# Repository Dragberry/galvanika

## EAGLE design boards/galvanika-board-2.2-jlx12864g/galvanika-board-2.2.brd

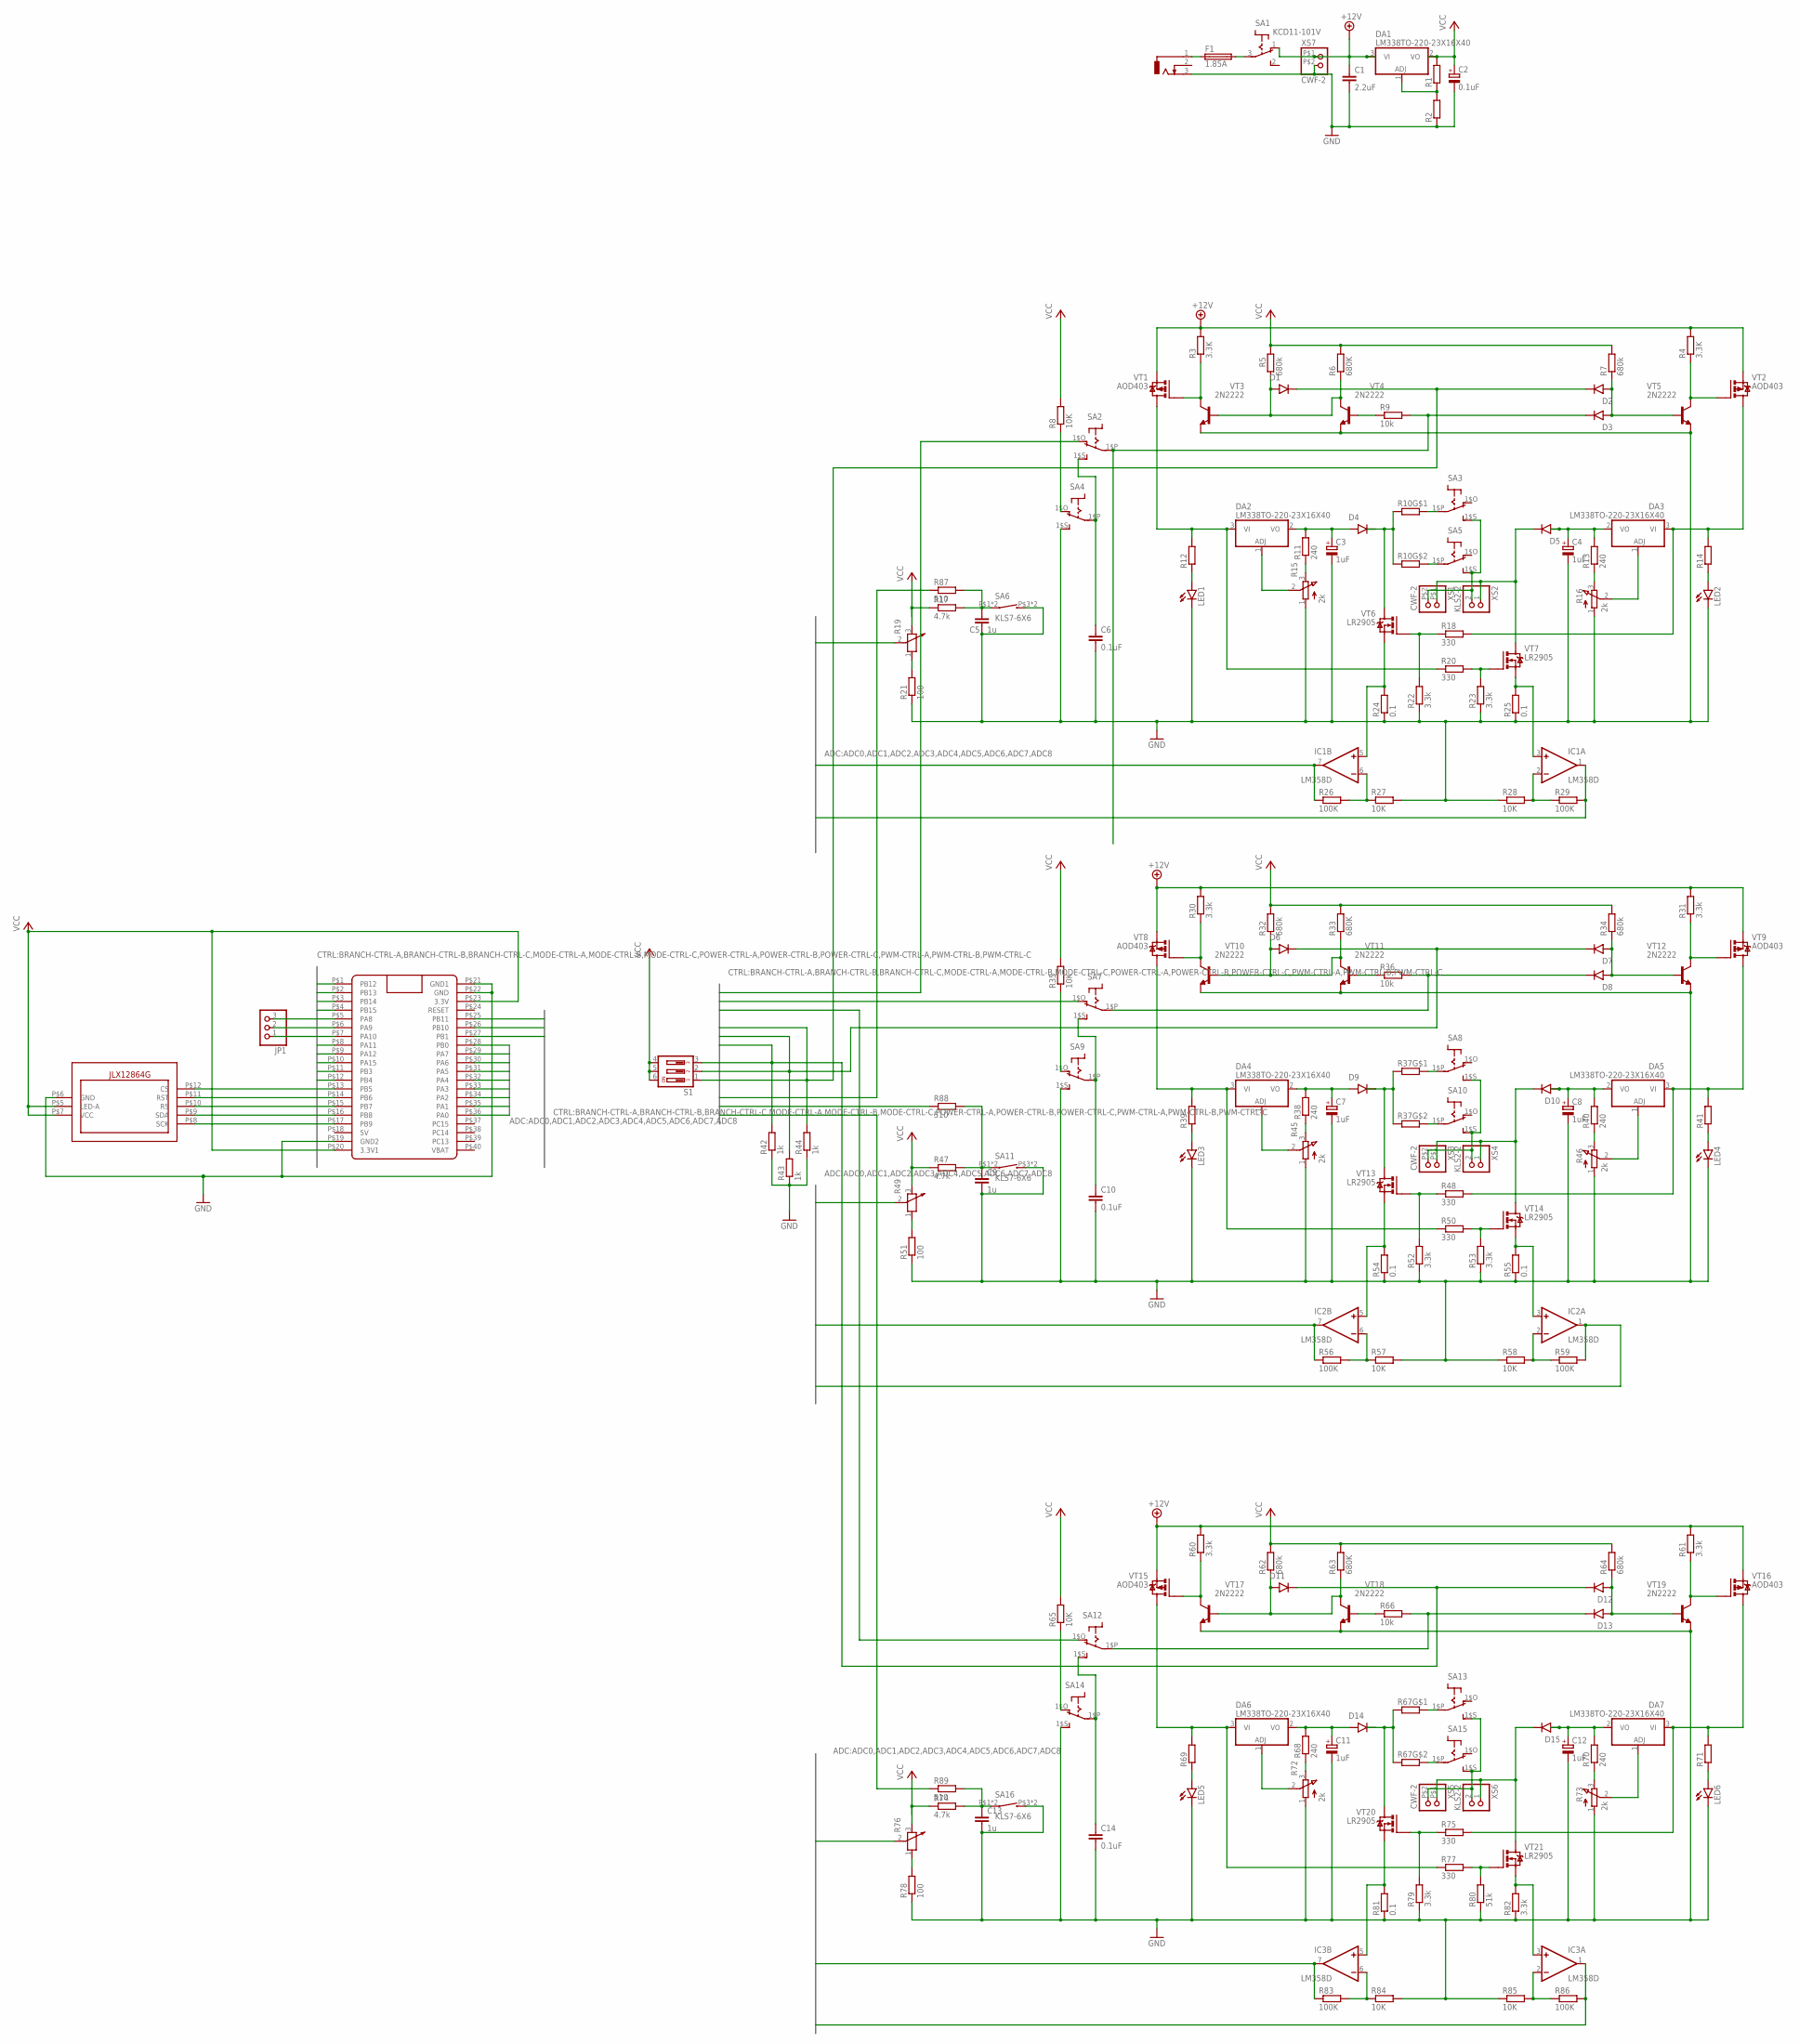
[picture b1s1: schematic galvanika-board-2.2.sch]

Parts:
C1: 2.2uF; C025-025X050
C2: 0.1uF; E2,5-5
C3, C4, C7, C8, C11, C12: 1uF; E5-4
C5, C9, C13: 1u; C1206
C6, C10, C14: 0.1uF; C1206
D1, D2, D3, D4, D5, D6, D7, D8, D9, D10, D11, D12, D13, D14, D15: 1N4001; DO41-10
DA1, DA2, DA3, DA4, DA5, DA6, DA7: LM338TO-220-23X16X40; TO220-23X16X40
DD1: BLUE_PILL
F1: 1.85A; MF-R
HG1: JLX12864G
IC1, IC2, IC3: LM358D; SO08
J1: DCJ0303
JP1: PINHD-1X3; 1X03
LED1, LED2, LED3, LED4, LED5, LED6: LED3MM
R1, R2, R12, R14, R39, R41, R69, R71: R-EU_0207/10; 0207/10
R3, R4: 3.3K; 0207/10
R5, R7, R32, R34, R62, R64: 680k; 0207/10
R6, R33, R63: 680K; 0207/10
R8, R35, R65: 10K; 0207/10
R9, R36, R66: 10k; 0207/10
R10, R37, R67: SQP-5W-2
R11, R13, R38, R40, R68, R70: 240; 0207/10
R15, R16, R45, R46, R72, R73: 2k; 3RP/1610N
R17, R47, R74: 4.7k; R1206
R18, R20, R48, R50, R75, R77: 330; 0207/10
R19, R49, R76: R0904N
R21, R51, R78: 100; R1206
R22, R23, R30, R31, R52, R53, R60, R61, R79: 3.3k; 0207/10
R24, R25, R54, R55, R81: 0.1; 0411/12
R26, R29, R56, R59, R83, R86: 100K; R1206
R27, R28, R57, R58, R84, R85: 10K; R1206
R42, R43, R44: 1k; R1206
R80: 51k; 0207/10
R82: 3.3k; 0411/12
R87, R88, R89: 510; R1206
S1: DS03; DS-03
SA1: KCD11-101V; KCD11-101-V
SA2, SA3, SA4, SA5, SA7, SA8, SA9, SA10, SA12, SA13, SA14, SA15: SS12D00DIP; SS12D00
SA6, SA11, SA16: KLS7-6X6
VT1, VT2, VT8, VT9, VT15, VT16: AOD403; TO252
VT3, VT4, VT5, VT10, VT11, VT12, VT17, VT18, VT19: 2N2222; TO92
VT6, VT7, VT13, VT14, VT20, VT21: LR2905; TO252
XS1, XS3, XS5, XS7: CWF-2
XS2, XS4, XS6: KLS2-2

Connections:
+12V: C1.1, DA1.3 (VI), R3.2, R4.2, R30.2, R31.2, R60.2, R61.2, SA1.1 (O), VT1.2 (S), VT2.2 (S), VT8.2 (S), VT9.2 (S), VT15.2 (S), VT16.2 (S), XS7.P$1 (1)
A-LEFT: IC1.3 (+IN), R25.2, VT7.2 (S)
A-LEFT1: IC2.3 (+IN), R55.2, VT14.2 (S)
A-LEFT2: IC3.3 (+IN), R82.2, VT21.2 (S)
A-RIGHT: IC1.5 (+IN), R24.2, VT6.2 (S)
A-RIGHT1: IC2.5 (+IN), R54.2, VT13.2 (S)
A-RIGHT2: IC3.5 (+IN), R81.2, VT20.2 (S)
ADC0: DD1.P$36 (PA0), R19.2 (3)
ADC1: DD1.P$35 (PA1), R49.2 (3)
ADC2: DD1.P$34 (PA2), IC1.7 (OUT), R26.1
ADC3: DD1.P$33 (PA3), IC1.1 (OUT), R29.2
ADC4: DD1.P$32 (PA4), R76.2 (3)
ADC5: DD1.P$31 (PA5), IC2.1 (OUT), R59.2
ADC6: DD1.P$30 (PA6), IC2.7 (OUT), R56.1
ADC7: DD1.P$29 (PA7), IC3.7 (OUT), R83.1
ADC8: DD1.P$28 (PB0), IC3.1 (OUT), R86.2
BRANCH-CTRL-A: D3.C (CATHODE), DD1.P$9 (PA12), R9.2, SA2.1$P
BRANCH-CTRL-B: D8.C (CATHODE), DD1.P$8 (PA11), R36.2, SA7.1$P
BRANCH-CTRL-C: D13.C (CATHODE), DD1.P$4 (PB15), R66.2, SA12.1$P
GND: C1.2, C2.-, C3.-, C4.-, C5.2, C6.2, C7.-, C8.-, C9.2, C10.2, C11.-, C12.-, C13.2, C14.2, DD1.P$19 (GND2), DD1.P$21 (GND1), DD1.P$22 (GND), HG1.P$6 (GND), IC1.4 (V-), IC2.4 (V-), IC3.4 (V-), J1.3, LED1.K (C), LED2.K (C), LED3.K (C), LED4.K (C), LED5.K (C), LED6.K (C), R2.1, R15.1 (A), R16.1 (A), R21.1, R22.1, R23.1, R24.1, R25.1, R27.2, R28.1, R42.1, R43.1, R44.1, R45.1 (A), R46.1 (A), R51.1, R52.1, R53.1, R54.1, R55.1, R57.2, R58.1, R72.1 (A), R73.1 (A), R78.1, R79.1, R80.1, R81.1, R82.1, R84.2, R85.1, SA4.1$S (S), SA6.P$3 (2), SA6.P$4 (2), SA9.1$S (S), SA11.P$3 (2), SA11.P$4 (2), SA14.1$S (S), SA16.P$3 (2), SA16.P$4 (2), VT3.3 (E), VT4.3 (E), VT5.3 (E), VT10.3 (E), VT11.3 (E), VT12.3 (E), VT17.3 (E), VT18.3 (E), VT19.3 (E), XS7.P$2 (2)
MODE-CTRL-A: DD1.P$12 (PB4), R87.1
MODE-CTRL-B: DD1.P$11 (PB3), R88.1
MODE-CTRL-C: DD1.P$10 (PA15), R89.1
unnamed: R3.1, VT1.1 (G), VT3.1 (C)
unnamed: DD1.P$15 (PB7), HG1.P$10 (RS)
unnamed: R10.4 (2), SA5.1$P
unnamed: DA1.1 (ADJ), R1.1, R2.2
unnamed: R30.1, VT8.1 (G), VT10.1 (C)
unnamed: R9.1, VT4.2 (B)
unnamed: D1.A (ANODE), R5.1, R6.1, VT3.2 (B), VT4.1 (C)
unnamed: LED1.A, R12.1
unnamed: R11.1, R15.3 (E)
unnamed: DA2.1 (ADJ), R15.2 (S)
unnamed: DD1.P$14 (PB6), HG1.P$11 (RST)
unnamed: R18.1, R22.2, VT6.1 (G)
unnamed: D4.C (CATHODE), R10.1, R10.3 (1), VT6.3 (D)
unnamed: R10.2, SA3.1$P
unnamed: R20.2, R23.2, VT7.1 (G)
unnamed: D2.A (ANODE), D3.A (ANODE), R7.1, VT5.2 (B)
unnamed: C5.1, R17.2, R87.2, SA6.P$1 (1), SA6.P$2 (1)
unnamed: R36.1, VT11.2 (B)
unnamed: LED2.A, R14.1
unnamed: R4.1, VT2.1 (G), VT5.1 (C)
unnamed: R13.1, R16.3 (E)
unnamed: LED3.A, R39.1
unnamed: DA3.1 (ADJ), R16.2 (S)
unnamed: DA4.1 (ADJ), R45.2 (S)
unnamed: D9.C (CATHODE), R37.1, R37.3 (1), VT13.3 (D)
unnamed: IC1.6 (-IN), R26.2, R27.1
unnamed: IC1.2 (-IN), R28.2, R29.1
unnamed: C9.1, R47.2, R88.2, SA11.P$1 (1), SA11.P$2 (1)
unnamed: DA5.1 (ADJ), R46.2 (S)
unnamed: LED4.A, R41.1
unnamed: R31.1, VT9.1 (G), VT12.1 (C)
unnamed: C13.1, R74.2, R89.2, SA16.P$1 (1), SA16.P$2 (1)
unnamed: IC2.6 (-IN), R56.2, R57.1
unnamed: IC2.2 (-IN), R58.2, R59.1
unnamed: DD1.P$5 (PA8), JP1.3
unnamed: D10.C (CATHODE), VT14.3 (D), XS3.P$1 (1), XS4.1
unnamed: R37.4 (2), SA10.1$P
unnamed: R37.2, SA8.1$P
unnamed: SA8.1$S (S), SA10.1$S (S), XS3.P$2 (2), XS4.2
unnamed: R48.1, R52.2, VT13.1 (G)
unnamed: R50.2, R53.2, VT14.1 (G)
unnamed: R38.1, R45.3 (E)
unnamed: R40.1, R46.3 (E)
unnamed: C10.1, SA7.1$S (S), SA9.1$P
unnamed: DD1.P$6 (PA9), JP1.2
unnamed: D6.A (ANODE), R32.1, R33.1, VT10.2 (B), VT11.1 (C)
unnamed: D7.A (ANODE), D8.A (ANODE), R34.1, VT12.2 (B)
unnamed: DD1.P$7 (PA10), JP1.1
unnamed: R60.1, VT15.1 (G), VT17.1 (C)
unnamed: R66.1, VT18.2 (B)
unnamed: LED5.A, R69.1
unnamed: DA6.1 (ADJ), R72.2 (S)
unnamed: D14.C (CATHODE), R67.1, R67.3 (1), VT20.3 (D)
unnamed: DA7.1 (ADJ), R73.2 (S)
unnamed: LED6.A, R71.1
unnamed: R61.1, VT16.1 (G), VT19.1 (C)
unnamed: D5.C (CATHODE), VT7.3 (D), XS1.P$1 (1), XS2.1
unnamed: F1.1, J1.1
unnamed: SA3.1$S (S), SA5.1$S (S), XS1.P$2 (2), XS2.2
unnamed: IC3.6 (-IN), R83.2, R84.1
unnamed: F1.2, SA1.3
unnamed: IC3.2 (-IN), R85.2, R86.1
unnamed: D15.C (CATHODE), VT21.3 (D), XS5.P$1 (1), XS6.1
unnamed: R67.4 (2), SA15.1$P
unnamed: R67.2, SA13.1$P
unnamed: SA13.1$S (S), SA15.1$S (S), XS5.P$2 (2), XS6.2
unnamed: R75.1, R79.2, VT20.1 (G)
unnamed: R77.2, R80.2, VT21.1 (G)
unnamed: R68.1, R72.3 (E)
unnamed: R70.1, R73.3 (E)
unnamed: C14.1, SA12.1$S (S), SA14.1$P
unnamed: DD1.P$16 (PB8), HG1.P$9 (SDA)
unnamed: D11.A (ANODE), R62.1, R63.1, VT17.2 (B), VT18.1 (C)
unnamed: D12.A (ANODE), D13.A (ANODE), R64.1, VT19.2 (B)
unnamed: DD1.P$17 (PB9), HG1.P$8 (SCK)
unnamed: DD1.P$13 (PB5), HG1.P$12 (CS)
unnamed: R19.1, R21.2
unnamed: R49.1, R51.2
unnamed: C6.1, SA2.1$S (S), SA4.1$P
unnamed: R76.1, R78.2
POWER-CTRL-A: D1.C (CATHODE), D2.C (CATHODE), DD1.P$27 (PB1), R44.2, S1.1
POWER-CTRL-B: D6.C (CATHODE), D7.C (CATHODE), DD1.P$26 (PB10), R43.2, S1.2
POWER-CTRL-C: D11.C (CATHODE), D12.C (CATHODE), DD1.P$25 (PB11), R42.2, S1.3
PWM-CTRL-A: DD1.P$2 (PB13), SA2.1$O (O)
PWM-CTRL-B: DD1.P$3 (PB14), SA7.1$O (O)
PWM-CTRL-C: DD1.P$1 (PB12), SA12.1$O (O)
RIGHT-EN: R8.1, SA4.1$O (O)
RIGHT-EN1: R35.1, SA9.1$O (O)
RIGHT-EN2: R65.1, SA14.1$O (O)
VCC: C2.+, DA1.2 (VO), DD1.P$20 (3.3V1), DD1.P$23 (3.3V), HG1.P$5 (LED-A), HG1.P$7 (VCC), IC1.8 (V+), IC2.8 (V+), IC3.8 (V+), R1.2, R5.2, R6.2, R7.2, R8.2, R17.1, R19.3 (2), R32.2, R33.2, R34.2, R35.2, R47.1, R49.3 (2), R62.2, R63.2, R64.2, R65.2, R74.1, R76.3 (2), S1.4, S1.5, S1.6
VI-LEFT: DA2.3 (VI), R12.2, R20.1, VT1.3 (D)
VI-LEFT1: DA4.3 (VI), R39.2, R50.1, VT8.3 (D)
VI-LEFT2: DA6.3 (VI), R69.2, R77.1, VT15.3 (D)
VI-RIGHT: DA3.3 (VI), R14.2, R18.2, VT2.3 (D)
VI-RIGHT1: DA5.3 (VI), R41.2, R48.2, VT9.3 (D)
VI-RIGHT2: DA7.3 (VI), R71.2, R75.2, VT16.3 (D)
VO-LEFT: C3.+, D4.A (ANODE), DA2.2 (VO), R11.2
VO-LEFT1: C7.+, D9.A (ANODE), DA4.2 (VO), R38.2
VO-LEFT2: C11.+, D14.A (ANODE), DA6.2 (VO), R68.2
VO-RIGHT: C4.+, D5.A (ANODE), DA3.2 (VO), R13.2
VO-RIGHT1: C8.+, D10.A (ANODE), DA5.2 (VO), R40.2
VO-RIGHT2: C12.+, D15.A (ANODE), DA7.2 (VO), R70.2

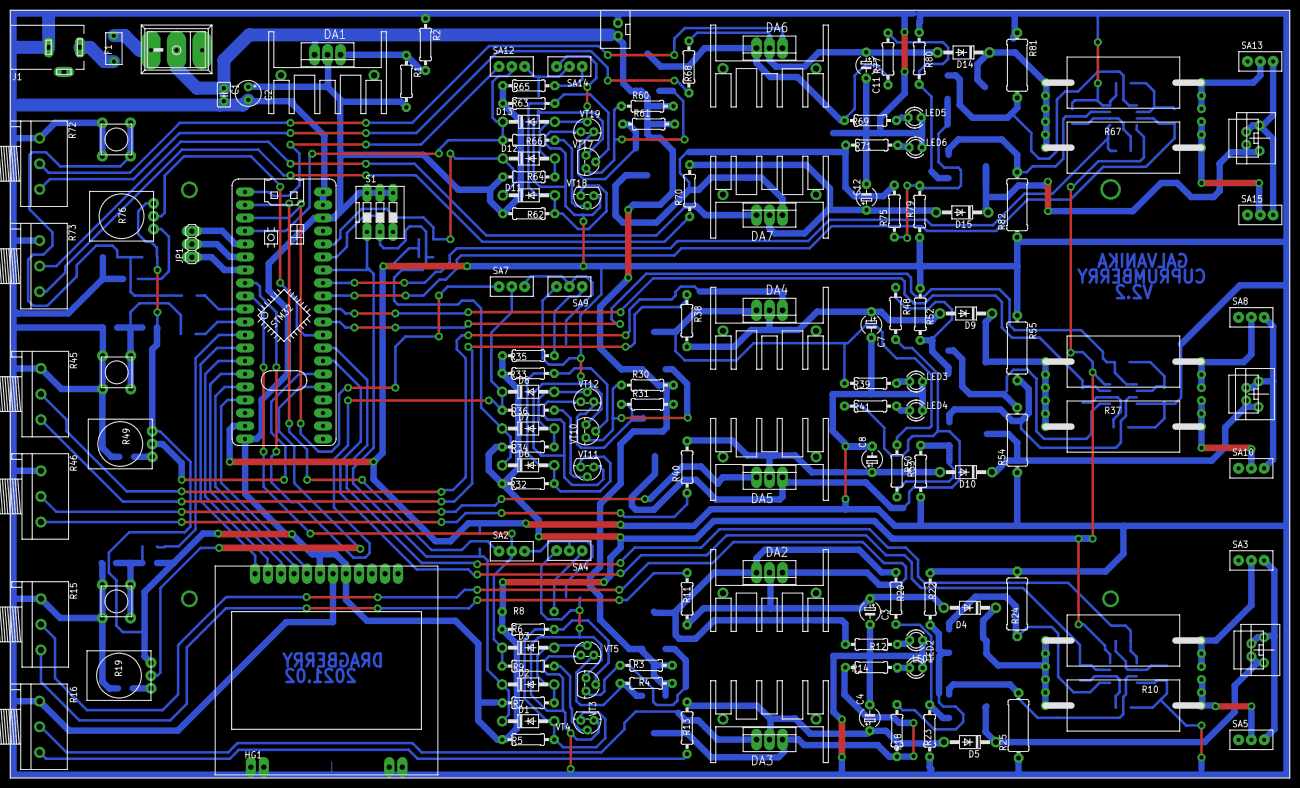
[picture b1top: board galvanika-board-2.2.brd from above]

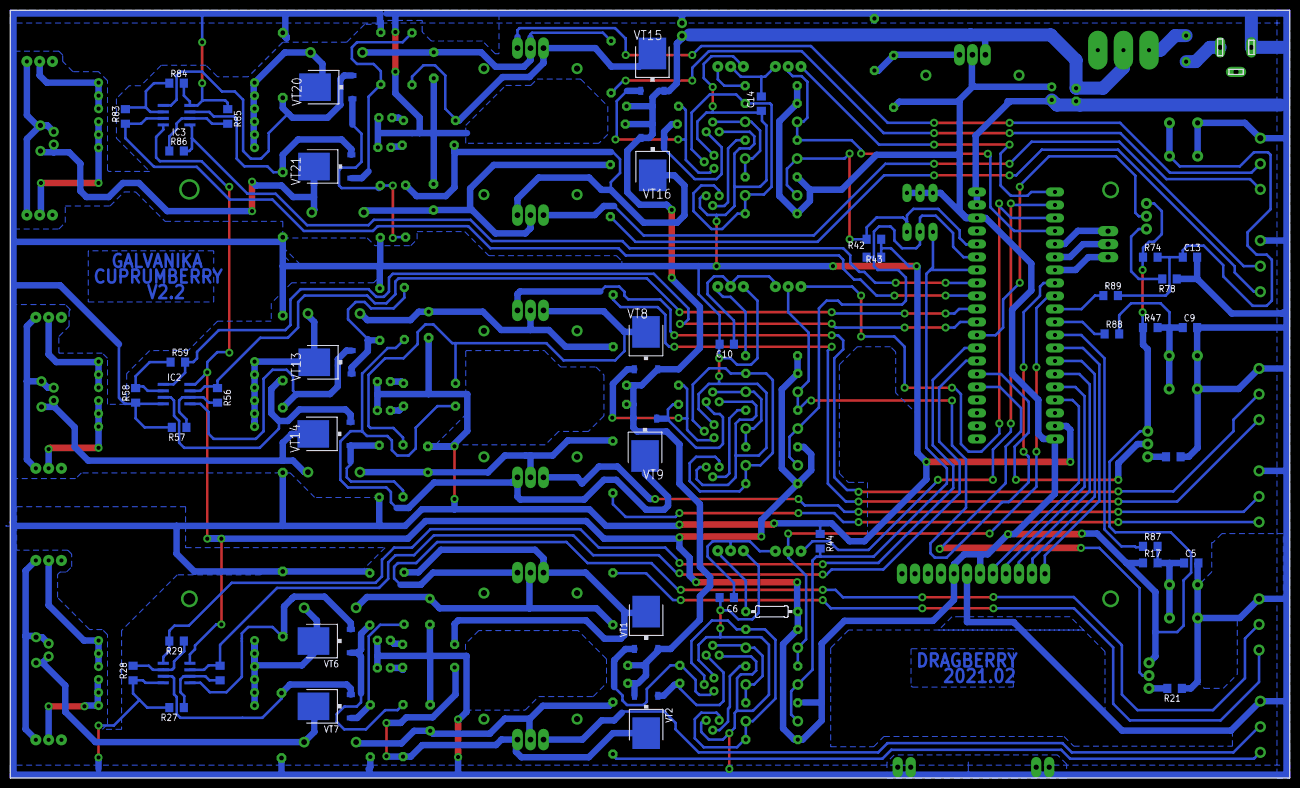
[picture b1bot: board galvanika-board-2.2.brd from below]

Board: 2 copper layers, 250.0 x 150.0 mm, 184 parts (46 on the bottom side), 125 nets.

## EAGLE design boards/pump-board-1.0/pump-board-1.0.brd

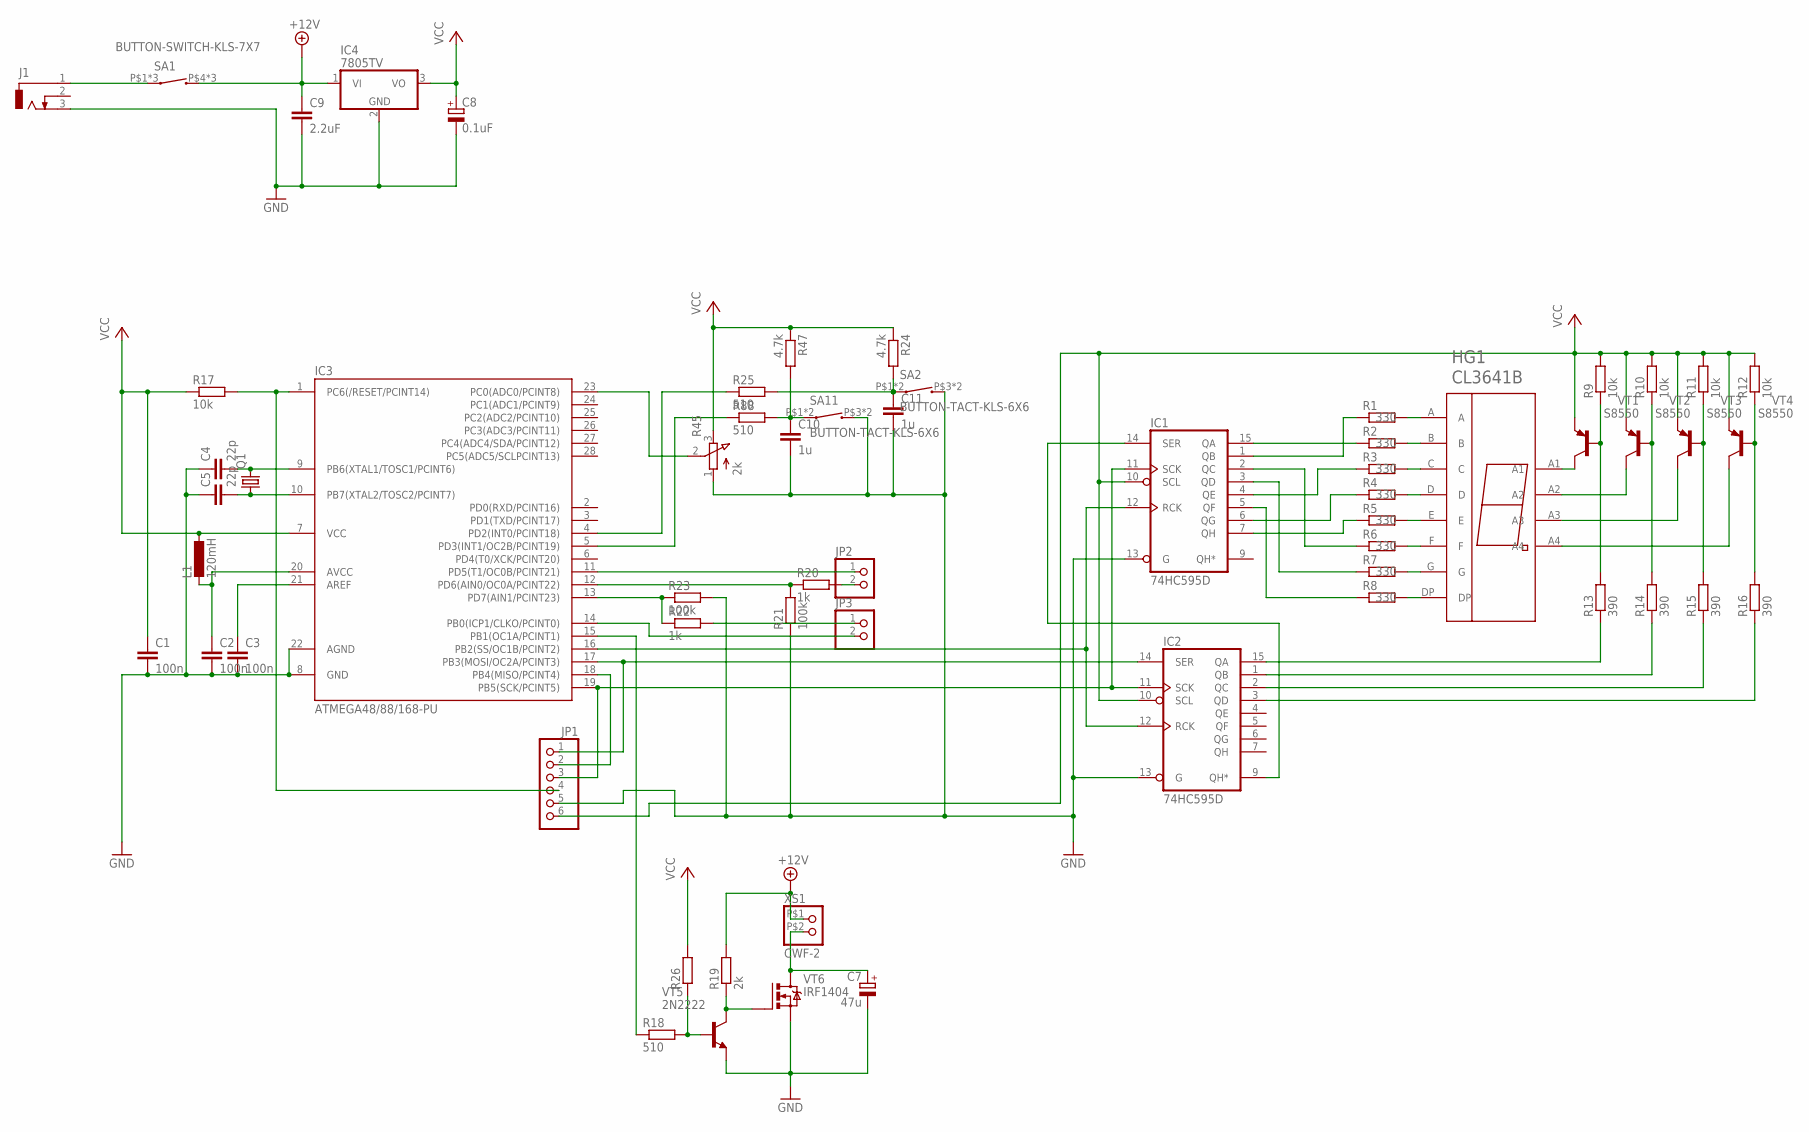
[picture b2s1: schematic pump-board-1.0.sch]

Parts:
C1: 100n; C025-025X050
C2, C3: 100n; C1206
C4, C5: 22p; C1206
C7: 47u; E2,5-5
C8: 0.1uF; E2,5-5
C9: 2.2uF; C025-025X050
C10, C11: 1u; C1206
HG1: CL3641B
IC1, IC2: 74HC595D; SO16
IC3: ATMEGA48/88/168-PU; DIL28-3
IC4: 7805TV; TO220V
J1: DCJ0303
JP1: PINHD-1X6; 1X06
JP2, JP3: PINHD-1X2; 1X02
L1: 120mH; 0207/10
Q1: CRYSTALHC49S; HC49/S
R1, R2, R3, R4, R5, R6, R7, R8: 330; R1206
R9, R10, R11, R12: 10k; R1206
R13, R14, R15, R16: 390; R1206
R17: 10k; 0207/10
R18: 510; 0207/10
R19: 2k; R1206
R20, R22: 1k; R1206
R21, R23: 100k; R1206
R24, R47: 4.7k; R1206
R25, R88: 510; R1206
R26: R-EU_R1206; R1206
R45: 2k; 3RP/1610N
SA1: BUTTON-SWITCH-KLS-7X7; KSL7-7X7
SA2, SA11: BUTTON-TACT-KLS-6X6; KLS7-6X6
VT1, VT2, VT3, VT4: S8550; TO92
VT5: 2N2222; TO92
VT6: IRF1404; TO220-V
XS1: CWF-2

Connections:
+12V: C9.1, IC4.1 (VI), R19.2, SA1.P$4 (2), SA1.P$5 (2), SA1.P$6 (2), XS1.P$1 (1)
ADC1: IC3.23 (PC0(ADC0/PCINT8)), R45.2 (S)
GND: C1.2, C2.2, C3.2, C4.1, C5.1, C7.-, C8.-, C9.2, C10.2, C11.2, IC1.8 (GND), IC1.13 (G), IC2.8 (GND), IC2.13 (G), IC3.8 (GND), IC3.22 (AGND), IC4.2 (GND), J1.3, JP1.5, R21.1, R23.2, R45.1 (A), SA2.P$3 (2), SA2.P$4 (2), SA11.P$3 (2), SA11.P$4 (2), VT5.3 (E), VT6.S
MODE-CTRL-B: IC3.5 (PD3(INT1/OC2B/PCINT19)), R88.1
unnamed: HG1.A1, VT1.1 (C)
unnamed: HG1.A2, VT2.1 (C)
unnamed: HG1.A3, VT3.1 (C)
unnamed: HG1.A4, VT4.1 (C)
unnamed: R9.1, R13.2, VT1.2 (B)
unnamed: R10.1, R14.2, VT2.2 (B)
unnamed: R11.1, R15.2, VT3.2 (B)
unnamed: R12.1, R16.2, VT4.2 (B)
unnamed: HG1.DP, R8.2
unnamed: HG1.G, R7.2
unnamed: HG1.F, R6.2
unnamed: IC2.15 (QA), R13.1
unnamed: HG1.E, R5.2
unnamed: HG1.D, R4.2
unnamed: HG1.C, R3.2
unnamed: HG1.B, R2.2
unnamed: HG1.A, R1.2
unnamed: IC2.1 (QB), R14.1
unnamed: IC2.2 (QC), R15.1
unnamed: IC2.3 (QD), R16.1
unnamed: IC1.15 (QA), R2.1
unnamed: IC1.1 (QB), R1.1
unnamed: IC1.2 (QC), R6.1
unnamed: IC1.4 (QE), R3.1
unnamed: IC1.7 (QH), R5.1
unnamed: IC1.5 (QF), R8.1
unnamed: IC1.3 (QD), R7.1
unnamed: IC1.6 (QG), R4.1
unnamed: IC1.14 (SER), IC2.9 (QH*)
unnamed: IC3.18 (PB4(MISO/PCINT4)), JP1.2
unnamed: IC1.12 (RCK), IC2.12 (RCK), IC3.16 (PB2(SS/OC1B/PCINT2))
unnamed: C3.1, IC3.21 (AREF)
unnamed: IC1.11 (SCK), IC2.11 (SCK), IC3.19 (PB5(SCK/PCINT5)), JP1.3
unnamed: IC3.1 (PC6(/RESET/PCINT14)), JP1.4, R17.2
unnamed: C2.1, IC3.20 (AVCC), L1.2
unnamed: C5.2, IC3.10 (PB7(XTAL2/TOSC2/PCINT7)), Q1.1
unnamed: C4.2, IC3.9 (PB6(XTAL1/TOSC1/PCINT6)), Q1.2
unnamed: R19.1, VT5.1 (C), VT6.G
unnamed: R18.2, R26.1, VT5.2 (B)
unnamed: C7.+, VT6.D, XS1.P$2 (2)
unnamed: IC3.15 (PB1(OC1A/PCINT1)), R18.1
unnamed: IC3.12 (PD6(AIN0/OC0A/PCINT22)), R20.1, R21.2
unnamed: IC3.11 (PD5(T1/OC0B/PCINT21)), JP2.1
unnamed: IC3.14 (PB0(ICP1/CLKO/PCINT0)), JP3.2
unnamed: IC3.13 (PD7(AIN1/PCINT23)), R22.1, R23.1
unnamed: JP3.1, R22.2
unnamed: JP2.2, R20.2
unnamed: C10.1, R47.2, R88.2, SA11.P$1 (1), SA11.P$2 (1)
unnamed: IC3.4 (PD2(INT0/PCINT18)), R25.1
unnamed: C11.1, R24.2, R25.2, SA2.P$1 (1), SA2.P$2 (1)
unnamed: IC2.14 (SER), IC3.17 (PB3(MOSI/OC2A/PCINT3)), JP1.1
unnamed: J1.1, SA1.P$1 (1), SA1.P$2 (1), SA1.P$3 (1)
VCC: C1.1, C8.+, IC1.10 (SCL), IC1.16 (VCC), IC2.10 (SCL), IC2.16 (VCC), IC3.7 (VCC), IC4.3 (VO), JP1.6, L1.1, R9.2, R10.2, R11.2, R12.2, R17.1, R24.1, R26.2, R45.3 (E), R47.1, VT1.3 (E), VT2.3 (E), VT3.3 (E), VT4.3 (E)

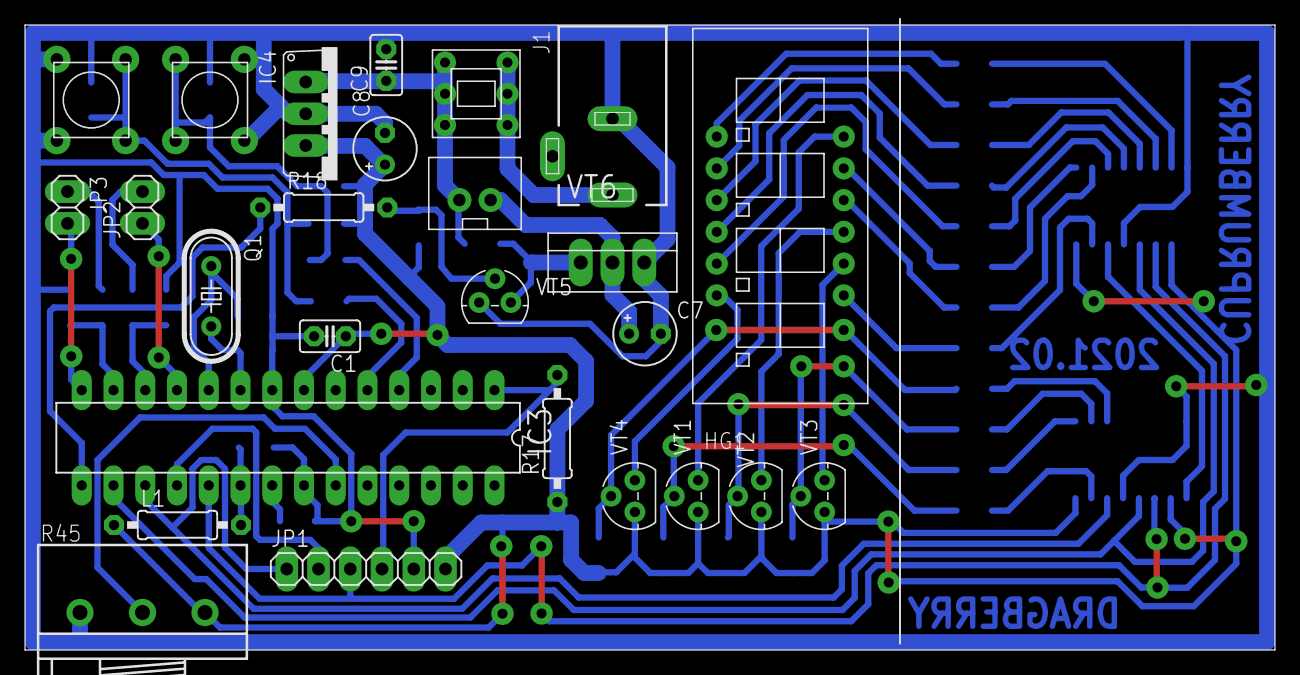
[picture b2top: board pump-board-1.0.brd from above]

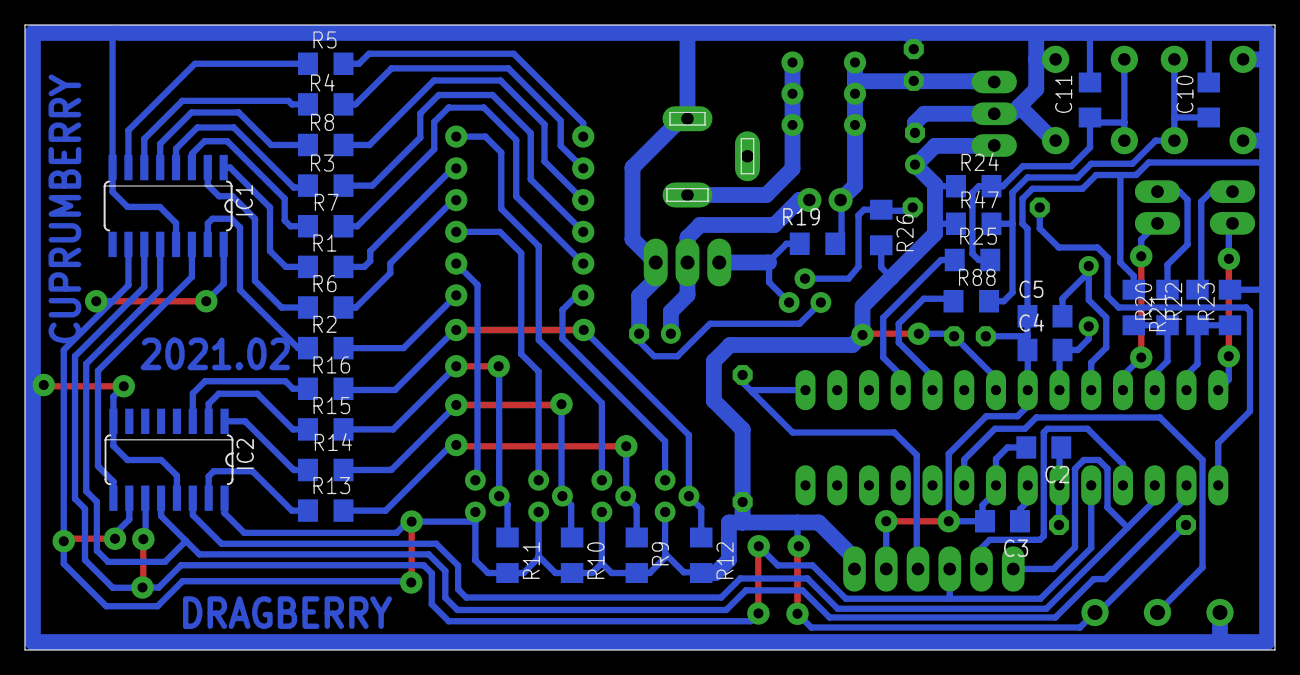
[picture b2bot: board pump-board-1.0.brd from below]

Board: 2 copper layers, 100.0 x 50.0 mm, 60 parts (34 on the bottom side), 57 nets.

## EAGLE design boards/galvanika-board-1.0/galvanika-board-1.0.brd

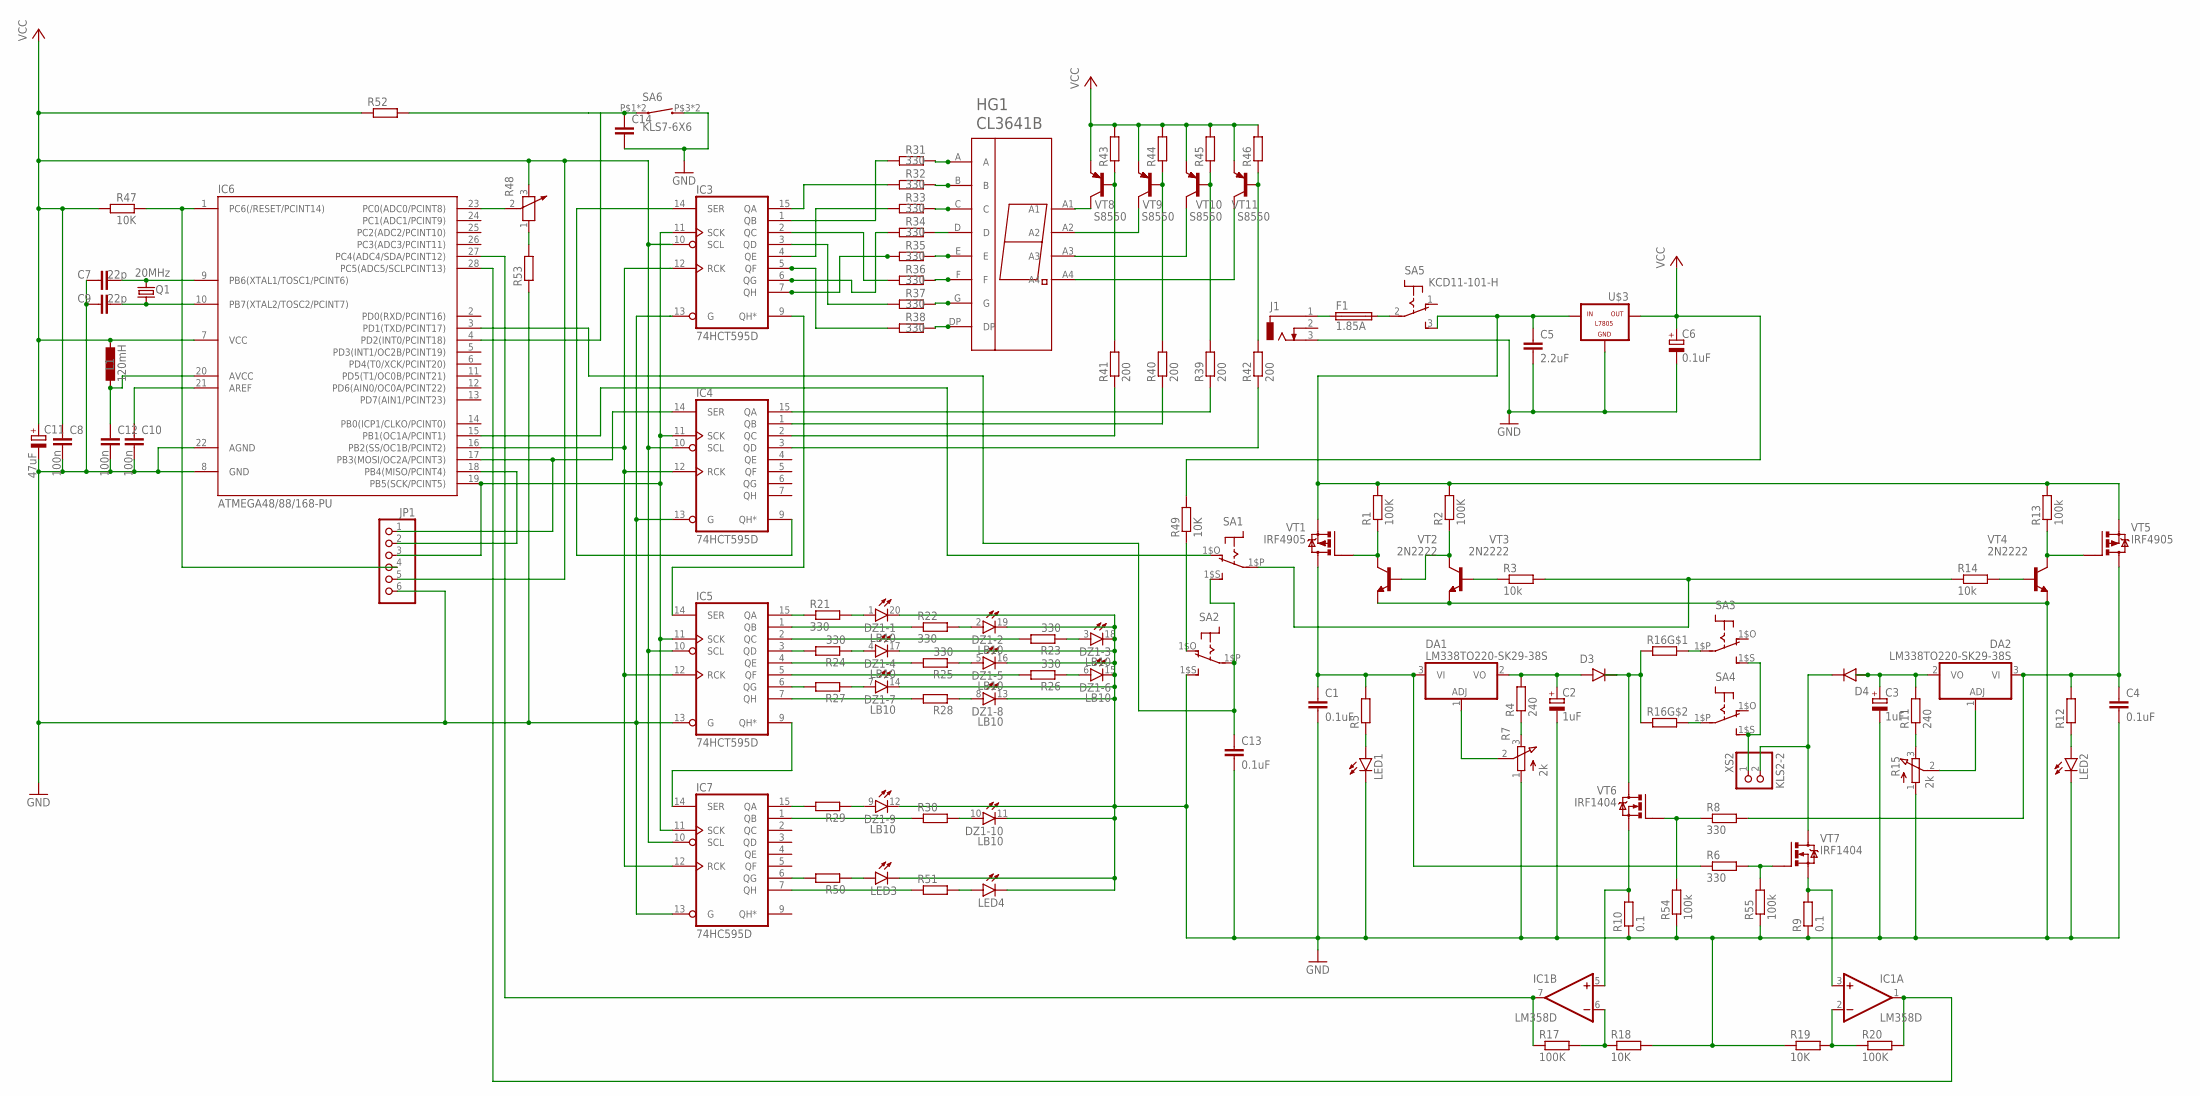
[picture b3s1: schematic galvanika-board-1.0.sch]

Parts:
C1, C4, C13: 0.1uF; C1206
C2, C3: 1uF; E5-4
C5: 2.2uF; C025-025X050
C6: 0.1uF; E2,5-5
C7, C9: 22p; C025-025X050
C8, C10, C12: 100n; C025-025X050
C11: 47uF; E2-4
C14: C-EUC1206; C1206
D3, D4: 1N4001; DO41-10
DA1, DA2: LM338TO220-SK29-38S; TO220-SK29-38S
DZ1: LB10
F1: 1.85A; MF-R
HG1: CL3641B
IC1: LM358D; SO08
IC3, IC4, IC5: 74HCT595D; SO16
IC6: ATMEGA48/88/168-PU; DIL28-3
IC7: 74HC595D; SO16
J1: DCJ0303
JP1: PINHD-1X6; 1X06
L1: 120mH; 0207/10
LED1, LED2, LED3, LED4: LED3MM
Q1: 20MHz; HC49/S
R1, R2: 100K; 0207/10
R3, R14: 10k; 0207/10
R4, R11: 240; 0207/10
R5, R12: R-EU_0207/10; 0207/10
R6, R8: 330; 0207/10
R7, R15: 2k; 3RP/1610N
R9, R10: 0.1; 0411/12
R13: 100k; 0207/10
R16: SQP-5W-2
R17, R20: 100K; R1206
R18, R19: 10K; R1206
R21, R22, R23, R24, R25, R26, R31, R32, R33, R34, R35, R36, R37, R38: 330; R1206
R27, R28, R29, R30, R43, R44, R45, R46, R50, R51, R52, R53: R-EU_R1206; R1206
R39, R40, R41, R42: 200; R1206
R47, R49: 10K; 0207/10
R48: R0904N
R54, R55: 100k; R1206
SA1, SA2, SA3, SA4: SS12D00DIP; SS12D00
SA5: KCD11-101-H
SA6: KLS7-6X6
U$3: L7805; TO220-SK29-38S
VT1, VT5: IRF4905; TO220-V
VT2, VT3, VT4: 2N2222; TO92
VT6, VT7: IRF1404; TO220-V
VT8, VT9, VT10, VT11: S8550; TO92
XS2: KLS2-2

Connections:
+19V: C5.1, R1.2, R2.2, R13.2, SA5.3 (S), U$3.1 (IN), VT1.S, VT5.S
A-LEFT: IC1.3 (+IN), R9.2, VT7.S
A-RIGHT: IC1.5 (+IN), R10.2, VT6.S
BRANCH-CTRL: R3.2, R14.1, SA1.1$P
CLOCK: IC3.11 (SCK), IC4.11 (SCK), IC5.11 (SCK), IC6.19 (PB5(SCK/PCINT5)), IC7.11 (SCK), JP1.3
DATA: IC3.14 (SER), IC4.9 (QH*)
GND: C1.2, C2.-, C3.-, C4.2, C5.2, C6.-, C7.1, C8.2, C9.1, C10.2, C11.-, C12.2, C13.2, C14.2, DZ1.11 (C), DZ1.12 (C), DZ1.13 (C), DZ1.14 (C), DZ1.15 (C), DZ1.16 (C), DZ1.17 (C), DZ1.18 (C), DZ1.19 (C), DZ1.20 (C), IC1.4 (V-), IC3.8 (GND), IC3.13 (G), IC4.8 (GND), IC4.13 (G), IC5.8 (GND), IC5.13 (G), IC6.8 (GND), IC6.22 (AGND), IC7.8 (GND), IC7.13 (G), J1.3, JP1.6, LED1.K (C), LED2.K (C), LED3.K (C), LED4.K (C), R7.1 (A), R9.1, R10.1, R15.1 (A), R18.2, R19.1, R53.1, R54.1, R55.1, SA2.1$S (S), SA6.P$3 (2), SA6.P$4 (2), U$3.2 (GND), VT2.3 (E), VT3.3 (E), VT4.3 (E)
LATCH: IC3.12 (RCK), IC4.12 (RCK), IC5.12 (RCK), IC6.16 (PB2(SS/OC1B/PCINT2)), IC7.12 (RCK)
MISO: IC6.18 (PB4(MISO/PCINT4)), JP1.2
MOSI: IC4.14 (SER), IC6.17 (PB3(MOSI/OC2A/PCINT3)), JP1.1
unnamed: R1.1, VT1.G, VT2.1 (C)
unnamed: R2.1, VT2.2 (B), VT3.1 (C)
unnamed: R16.4 (2), SA4.1$P
unnamed: IC5.15 (QA), R21.1
unnamed: HG1.D, R34.2
unnamed: R3.1, VT3.2 (B)
unnamed: IC3.4 (QE), R33.1
unnamed: LED1.A, R5.1
unnamed: R4.1, R7.3 (E)
unnamed: DA1.1 (ADJ), R7.2 (S)
unnamed: IC1.7 (OUT), IC6.27 (PC4(ADC4/SDA/PCINT12)), R17.1
unnamed: R8.1, R54.2, VT6.G
unnamed: D3.C (CATHODE), R16.1, R16.3 (1), VT6.D
unnamed: R16.2, SA3.1$P
unnamed: R6.2, R55.2, VT7.G
unnamed: IC3.1 (QB), R31.1
unnamed: IC3.7 (QH), R35.1
unnamed: DZ1.1 (A), R21.2
unnamed: LED2.A, R12.1
unnamed: R13.1, VT4.1 (C), VT5.G
unnamed: R11.1, R15.3 (E)
unnamed: R14.2, VT4.2 (B)
unnamed: DA2.1 (ADJ), R15.2 (S)
unnamed: IC7.6 (QG), R50.2
unnamed: IC1.6 (-IN), R17.2, R18.1
unnamed: IC1.2 (-IN), R19.2, R20.1
unnamed: IC1.1 (OUT), IC6.28 (PC5(ADC5/SCLPCINT13)), R20.2
unnamed: IC5.1 (QB), R22.1
unnamed: DZ1.2 (A), R22.2
unnamed: IC5.2 (QC), R23.2
unnamed: DZ1.3 (A), R23.1
unnamed: DZ1.4 (A), R24.1
unnamed: IC5.3 (QD), R24.2
unnamed: IC3.5 (QF), R38.1
unnamed: IC5.4 (QE), R25.2
unnamed: DZ1.5 (A), R25.1
unnamed: IC5.5 (QF), R26.2
unnamed: DZ1.6 (A), R26.1
unnamed: IC5.6 (QG), R27.2
unnamed: DZ1.7 (A), R27.1
unnamed: IC5.7 (QH), R28.2
unnamed: DZ1.8 (A), R28.1
unnamed: IC3.2 (QC), R36.1
unnamed: IC3.9 (QH*), IC5.14 (SER)
unnamed: IC7.7 (QH), R51.1
unnamed: IC5.9 (QH*), IC7.14 (SER)
unnamed: IC7.15 (QA), R29.2
unnamed: IC7.1 (QB), R30.1
unnamed: DZ1.10 (A), R30.2
unnamed: DZ1.9 (A), R29.1
unnamed: HG1.A, R31.2
unnamed: HG1.B, R32.2
unnamed: HG1.C, R33.2
unnamed: LED3.A, R50.1
unnamed: HG1.E, R35.2
unnamed: HG1.F, R36.2
unnamed: HG1.G, R37.2
unnamed: HG1.DP, R38.2
unnamed: D4.C (CATHODE), VT7.D, XS2.2
unnamed: IC3.15 (QA), R32.1
unnamed: F1.1, J1.1
unnamed: SA3.1$S (S), SA4.1$S (S), XS2.1
unnamed: IC3.3 (QD), R37.1
unnamed: F1.2, SA5.2
unnamed: IC3.6 (QG), R34.1
unnamed: LED4.A, R51.2
unnamed: IC4.15 (QA), R39.1
unnamed: IC4.1 (QB), R40.1
unnamed: IC4.2 (QC), R41.1
unnamed: IC4.3 (QD), R42.1
unnamed: R41.2, R43.1, VT8.2 (B)
unnamed: R40.2, R44.1, VT9.2 (B)
unnamed: R39.2, R45.1, VT10.2 (B)
unnamed: R42.2, R46.1, VT11.2 (B)
unnamed: HG1.A1, VT8.1 (C)
unnamed: HG1.A2, VT9.1 (C)
unnamed: HG1.A3, VT10.1 (C)
unnamed: HG1.A4, VT11.1 (C)
unnamed: C7.2, IC6.9 (PB6(XTAL1/TOSC1/PCINT6)), Q1.2
unnamed: C9.2, IC6.10 (PB7(XTAL2/TOSC2/PCINT7)), Q1.1
unnamed: C10.1, IC6.21 (AREF)
unnamed: C12.1, IC6.20 (AVCC), L1.2
unnamed: IC6.1 (PC6(/RESET/PCINT14)), JP1.4, R47.2
unnamed: C14.1, IC6.4 (PD2(INT0/PCINT18)), R52.2, SA6.P$1 (1), SA6.P$2 (1)
unnamed: R48.1, R53.2
unnamed: IC6.23 (PC0(ADC0/PCINT8)), R48.2 (3)
PWM: IC6.15 (PB1(OC1A/PCINT1)), SA1.1$O (O)
PWM-CTRL: C13.1, IC6.3 (PD1(TXD/PCINT17)), SA1.1$S (S), SA2.1$P
RIGHT-EN: R49.1, SA2.1$O (O)
VCC: C6.+, C8.1, C11.+, IC1.8 (V+), IC3.10 (SCL), IC3.16 (VCC), IC4.10 (SCL), IC4.16 (VCC), IC5.10 (SCL), IC5.16 (VCC), IC6.7 (VCC), IC7.10 (SCL), IC7.16 (VCC), JP1.5, L1.1, R43.2, R44.2, R45.2, R46.2, R47.1, R48.3 (2), R49.2, R52.1, U$3.3 (OUT), VT8.3 (E), VT9.3 (E), VT10.3 (E), VT11.3 (E)
VI-LEFT: C1.1, DA1.3 (VI), R5.2, R6.1, VT1.D
VI-RIGHT: C4.1, DA2.3 (VI), R8.2, R12.2, VT5.D
VO-LEFT: C2.+, D3.A (ANODE), DA1.2 (VO), R4.2
VO-RIGHT: C3.+, D4.A (ANODE), DA2.2 (VO), R11.2

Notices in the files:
parts and their libraries:
diy-modules: Released under the Creative Commons Attribution 4.0 International License: http://creativecommons.org/licenses/by/4.0
